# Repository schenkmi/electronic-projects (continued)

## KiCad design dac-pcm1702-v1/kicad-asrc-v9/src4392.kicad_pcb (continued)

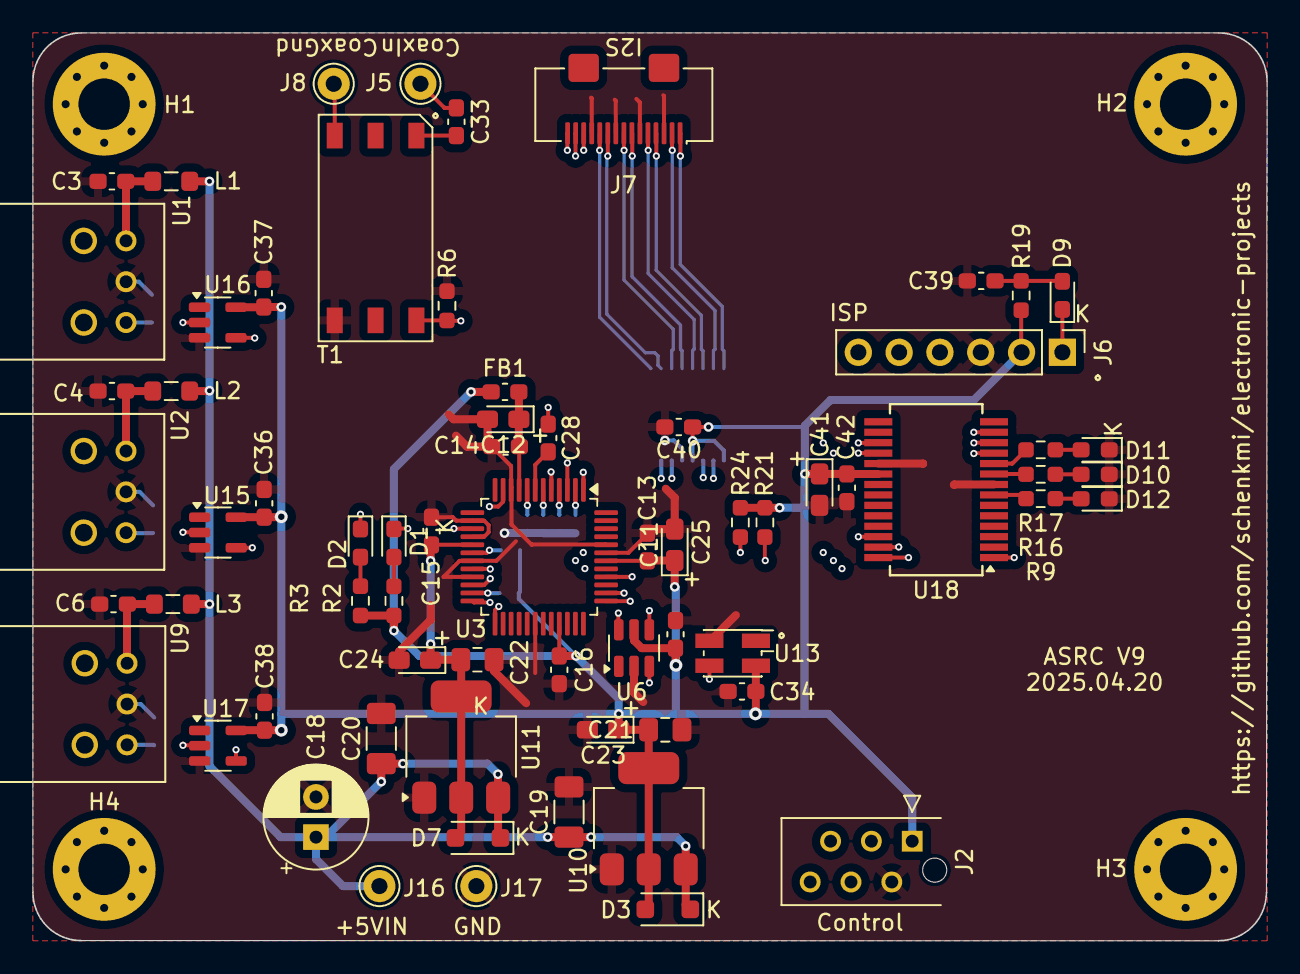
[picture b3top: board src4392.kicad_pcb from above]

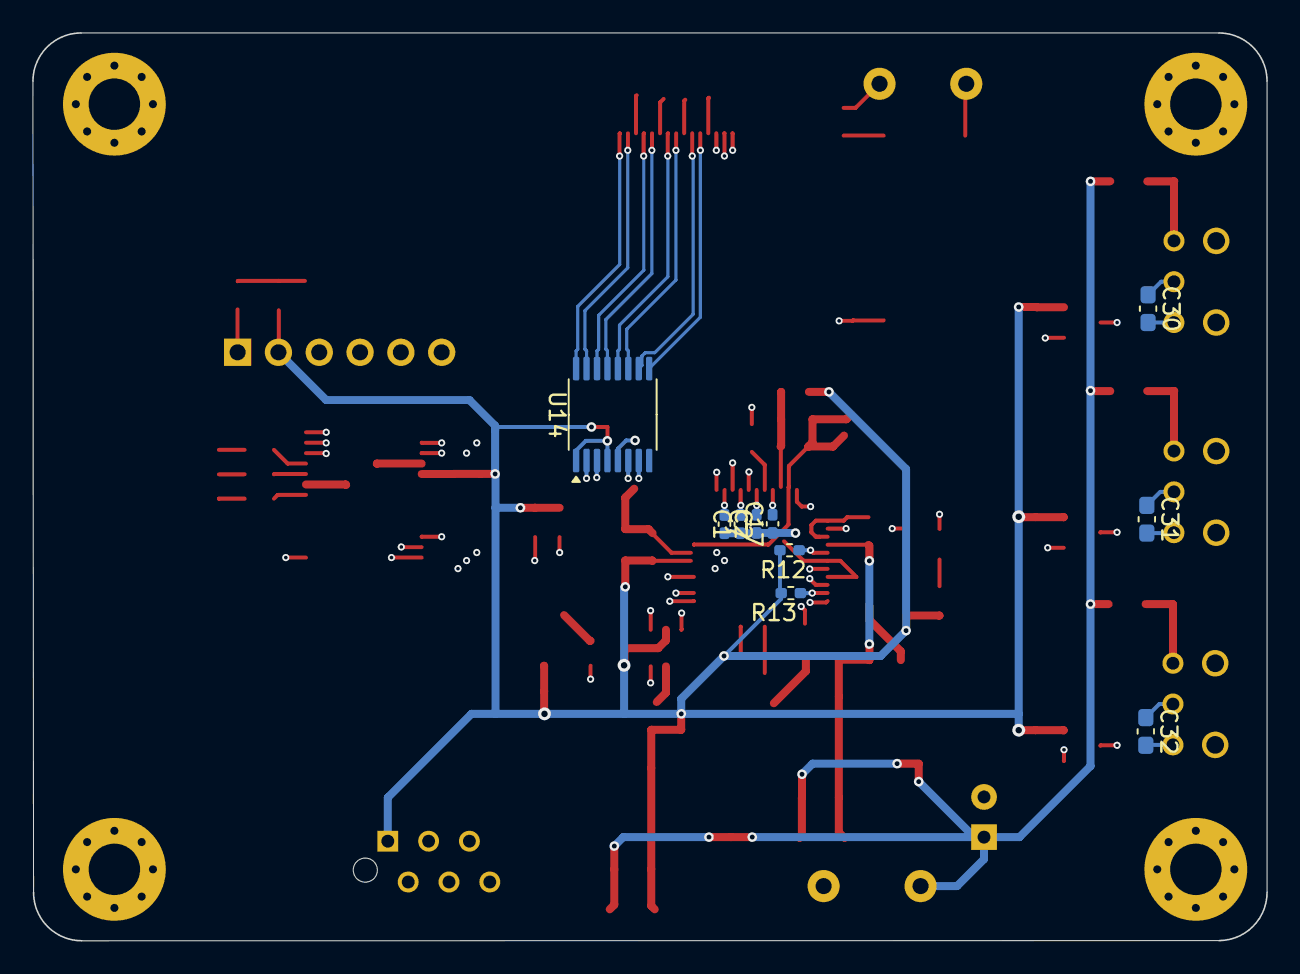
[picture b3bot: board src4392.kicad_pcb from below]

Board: 4 copper layers, 76.8 x 56.5 mm, 82 parts (10 on the bottom side), 59 nets.

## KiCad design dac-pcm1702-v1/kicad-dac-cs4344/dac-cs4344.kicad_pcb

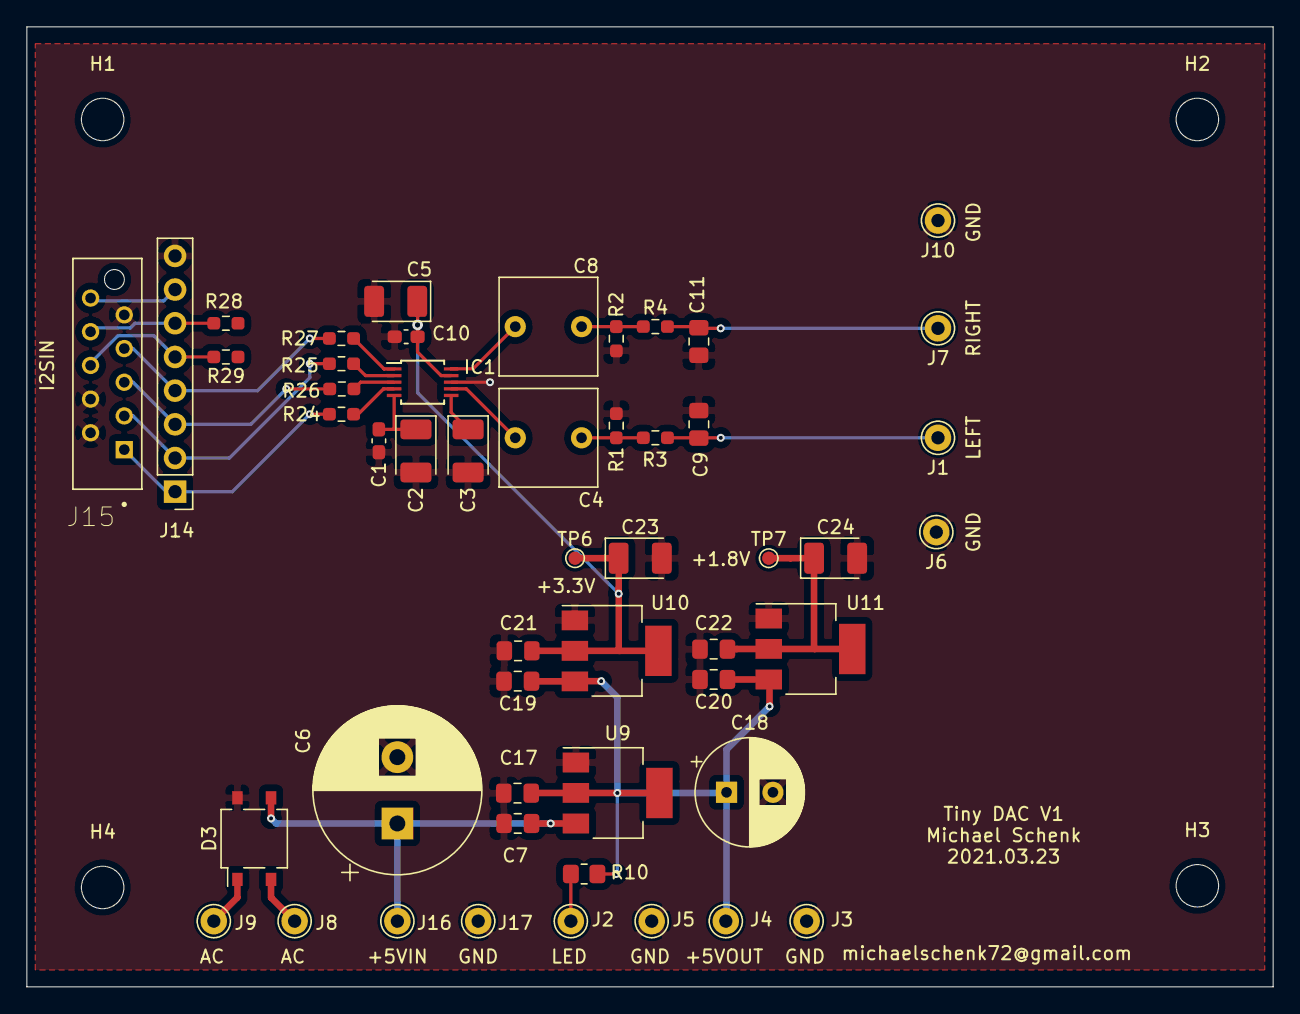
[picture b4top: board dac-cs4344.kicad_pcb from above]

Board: 2 copper layers, 94.0 x 72.4 mm, 55 parts (0 on the bottom side), 27 nets.

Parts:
C1, C5: 100nF; C_0603_1608Metric_Pad1.08x0.95mm_HandSolder
C2, C3, C10, C23, C24: 10uF; CP_EIA-3528-21_Kemet-B_Pad1.50x2.35mm_HandSolder
C4, C8: 3.3uF; C_Rect_L7.2mm_W7.2mm_P5.00mm_FKS2_FKP2_MKS2_MKP2
C6: 1000uF; CP_Radial_D12.5mm_P5.00mm
C7, C19, C20: 330nF; C_0805_2012Metric_Pad1.18x1.45mm_HandSolder
C9, C11: 2.7nF; C_0805_2012Metric_Pad1.18x1.45mm_HandSolder
C17, C21, C22: 100nF; C_0805_2012Metric_Pad1.18x1.45mm_HandSolder
C18: 100uF; CP_Radial_D8.0mm_P3.50mm
D3: MB4S; TO-269AA
H1, H2, H3, H4: MountingHole; MountingHole_3.2mm_M3
IC1: CS4344; TSSOP-10_3x3mm_P0.5mm
J1: LEFT; Pin_D1.0mm_L10.0mm
J2: LED; Pin_D1.0mm_L10.0mm
J3, J5, J6, J10, J17: GND; Pin_D1.0mm_L10.0mm
J4: +5VOUT; Pin_D1.0mm_L10.0mm
J7: RIGHT; Pin_D1.0mm_L10.0mm
J8, J9: AC; Pin_D1.0mm_L10.0mm
J14: PORTA; PinHeader_1x08_P2.54mm_Vertical
J15: A; TE_CONN_RCPT_10POS_0.1_TIN_PCB
J16: +5VIN; Pin_D1.0mm_L10.0mm
R1, R2: 10k; R_0603_1608Metric_Pad0.98x0.95mm_HandSolder
R3, R4: 470R; R_0603_1608Metric_Pad0.98x0.95mm_HandSolder
R10: 330R; R_0805_2012Metric_Pad1.20x1.40mm_HandSolder
R24, R25, R26, R27, R28, R29: 33R; R_0603_1608Metric_Pad0.98x0.95mm_HandSolder
TP6: 3.3V; TestPoint_Pad_D1.0mm
TP7: 1.8V; TestPoint_Pad_D1.0mm
U9: TLV1117-50; SOT-223-3_TabPin2
U10: TLV1117-33; SOT-223-3_TabPin2
U11: TLV1117-18; SOT-223-3_TabPin2

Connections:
+1V8: C22.1, C24.1, TP7.1, U11.2
+3V3: C5.2, C10.1, C21.1, C23.1, IC1.9, TP6.1, U10.2
BCKA: IC1.2, R25.2
GND: C1.1, C2.2, C3.2, C5.1, C6.2, C7.2, C9.1, C10.2, C11.1, C17.2, C18.2, C19.2, C20.2, C21.2, C22.2, C23.2, C24.2, D3.4, IC1.8, J3.1, J5.1, J6.1, J10.1, J14.8, J15.2, J15.4, J15.9, J17.1, R1.1, R2.1, U9.1, U10.1, U11.1
LRCKA: IC1.3, R26.2
MCLK: IC1.4, R24.2
unnamed: C1.2, C2.1, IC1.5
unnamed: C3.1, IC1.6
unnamed: C4.1, R1.2, R3.1
unnamed: C4.2, IC1.7
unnamed: C6.1, C7.1, D3.3, J16.1, U9.3
unnamed: C8.1, R2.2, R4.1
unnamed: C8.2, IC1.10
unnamed: C9.2, J1.1, R3.2
unnamed: C11.2, J7.1, R4.2
unnamed: C17.1, C18.1, C19.1, C20.1, J4.1, R10.2, U9.2, U10.3, U11.3
unnamed: D3.1, J9.1
unnamed: D3.2, J8.1
unnamed: J2.1, R10.1
unnamed: J14.1, J15.1, R24.1
unnamed: J14.2, J15.3, R25.1
unnamed: J14.3, J15.5, R26.1
unnamed: J14.4, J15.7, R27.1
unnamed: J14.5, J15.6, R29.2
unnamed: J14.6, J15.8, R28.2
RESET: J14.7, J15.10
SDOUTA: IC1.1, R27.2
